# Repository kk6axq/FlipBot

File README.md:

# FlipBot
FlipBot is a small two wheeled robot development platform. It was developed over the Spring 2021 semester as an honors contract project for EGR102, at Arizona State University on the Polytechnic Campus, under the guidance of Dr. Daniel Frank. The goal for this project was to develop a small robot platform and to gain a better understanding of the design considerations in designing a complete system. Where possible, this project attempted to integrate components directly into the design, rather than using breakout boards or modules.

 ## Components
 There are several major components of FlipBot:
 * **Controller.** The robot is controlled by a wireless remote connected to a Wii Nunchuk. This provides a joystick, two buttons, and pitch/roll data that is processed by a microcontroller and sent wirelessly to the main controller onboard the robot. The controller also has onboard battery management hardware to enable operation from a single 18650 battery.

 * **Wireless link.** The controller and robot use NRF24 radio modules to communicate. These operate in the 2.4GHz ISM band and provide low latency, medium range. While they have the ability to confirm packet reception, in this application the controller sends packets regardless of whether the received is in range or able to respond.
 * **Onboard Power Management.** This project was developed in conjunction with a second honors contract to develop a power management board for use with LiPo batteries. This PCB provides intelligent power monitoring capabilities on the robot. More information about this part is available in the project repository: [https://github.com/kk6axq/PowerMonitor/](https://github.com/kk6axq/PowerMonitor/).

 * **Orientation Sensing.** An onboard MPU6050 accelerometer/gyro provides onboard orientation detection, enabling the controls to be reversed if the robot flips upside down.
 * **Main Board.** The main PCB interfaces to the radio, orientation sensor, and the power management board, in addition to providing motor control and processing input from the motor's encoders (not yet implemented).

## Project Status
Due to incomplete design verification and limited time, the project was not able to achieve full functionality before the end of the semester. The level converter responsible for interfacing between the motor controllers and the microcontroller was not properly matched to the application and would not properly convert, leading the motor controllers to operate sporadically.

This issue, in addition to a few minor routing decisions, is due to be fixed during a revision of the main board scheduled for Summer 2021, with the hope that the project will be functional by Fall 2021.

**Update Fall 2021:** Over the summer, the hardware design issues were mitigated within the existing PCB and a new PCB was milled for the controller. There still remain some phantom issues with controller connectivity and some larger issues with the initial current draw of the motor controllers. At this point, the project is at a holding point, and may or may not see further development.

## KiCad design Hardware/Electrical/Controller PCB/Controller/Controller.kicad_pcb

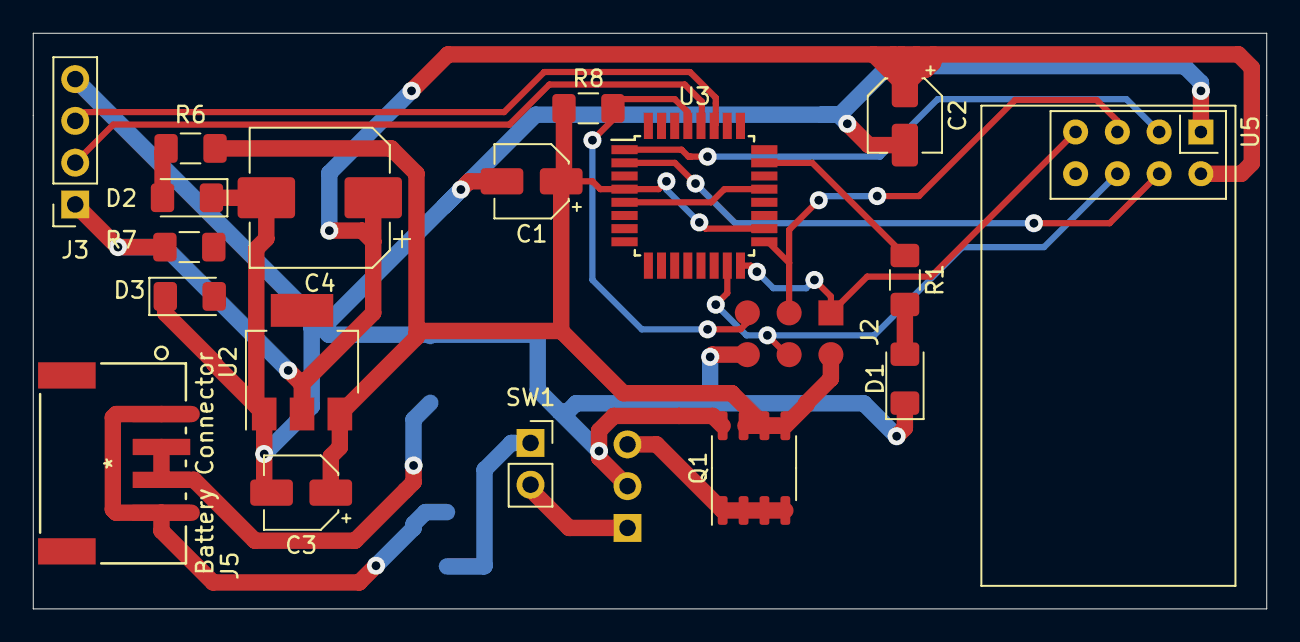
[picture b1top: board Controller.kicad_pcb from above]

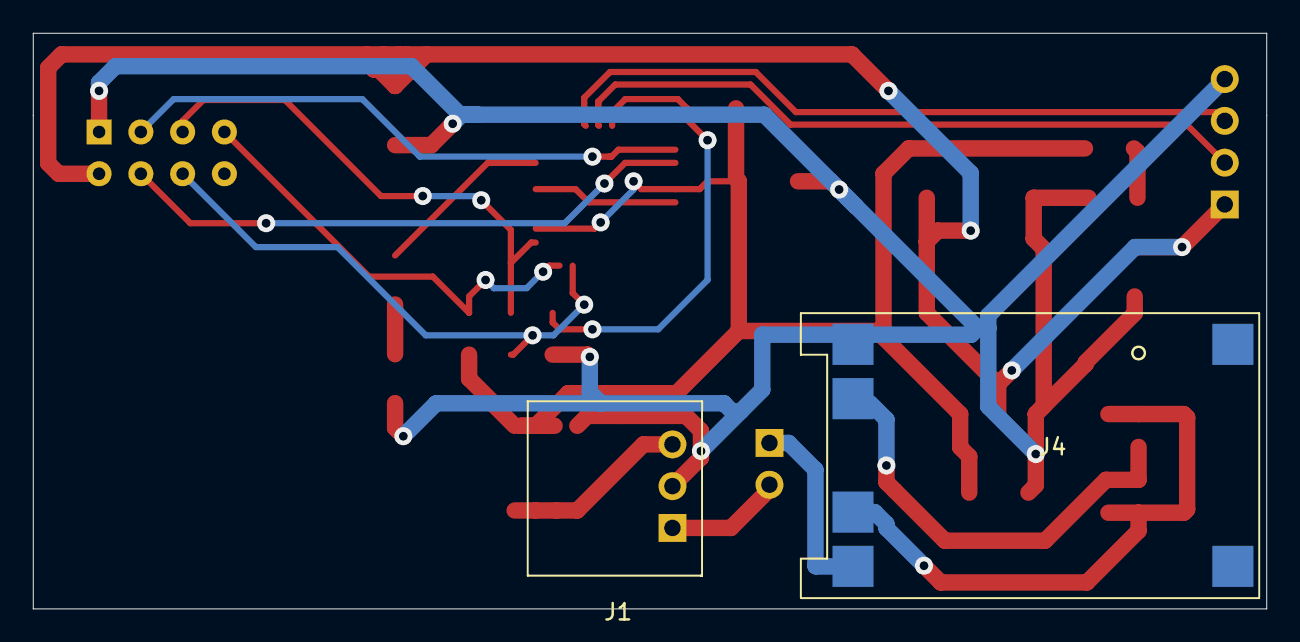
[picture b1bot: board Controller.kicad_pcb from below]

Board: 2 copper layers, 75.0 x 35.0 mm, 21 parts (2 on the bottom side), 21 nets.

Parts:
C1, C2, C3: 10uF; CP_Elec_4x3.9
C4: 100uF; CP_Elec_8x10
D1, D2: Red; LED_1206_3216Metric_Pad1.42x1.75mm_HandSolder
D3: Green; LED_1206_3216Metric_Pad1.42x1.75mm_HandSolder
J1: Boost Board; Boost_Converter
J2: AVR-ISP-6; ICSP
J3: Nunchuk Connector; PinSocket_1x04_P2.54mm_Vertical
J4: Charge Controller; Battery_Manager
J5: Battery Connector; S4B-PH-SM4-TBLFSN
Q1: Si4435FDY; Si4435
R1, R6: 330; R_1206_3216Metric_Pad1.42x1.75mm_HandSolder
R7: 220; R_1206_3216Metric_Pad1.42x1.75mm_HandSolder
R8: 10k; R_1206_3216Metric_Pad1.42x1.75mm_HandSolder
SW1: SW_SPST; PinSocket_1x02_P2.54mm_Vertical
U2: LM1117-3.3; SOT-223
U3: ATtiny88-AU; TQFP-32_7x7mm_P0.8mm
U5: NRF24L01_Breakout; nRF24L01_Breakout

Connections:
+3V3: C2.1, C4.1, J3.1, R7.1, U2.2, U5.2
+5V: C1.1, C3.1, J2.2, Q1.1, Q1.2, Q1.3, R6.1, R8.1, U2.3, U3.4, U3.18
CE: U3.1, U5.3
CSN: U3.2, U5.4
GND: C1.2, C2.2, C3.2, C4.2, D1.1, D2.1, D3.1, J1.2, J2.6, J3.4, J4.4, Q1.4, U2.1, U5.1
LED_STATUS: R1.1, U3.23
MISO: J2.1, U3.16, U5.7
MOSI: J2.4, U3.15, U5.6
unnamed: D1.2, R1.2
unnamed: D2.2, R6.2
unnamed: D3.2, R7.2
unnamed: J1.1, SW1.2
unnamed: J1.3, Q1.5, Q1.6, Q1.7, Q1.8
unnamed: J4.1, SW1.1
unnamed: J4.2, J5.1, J5.4
unnamed: J4.3, J5.2, J5.3
unnamed: U3.5, U3.21
RST: J2.5, R8.2, U3.29
SCK: J2.3, U3.17, U5.5
SCL: J3.2, U3.28
SDA: J3.3, U3.27

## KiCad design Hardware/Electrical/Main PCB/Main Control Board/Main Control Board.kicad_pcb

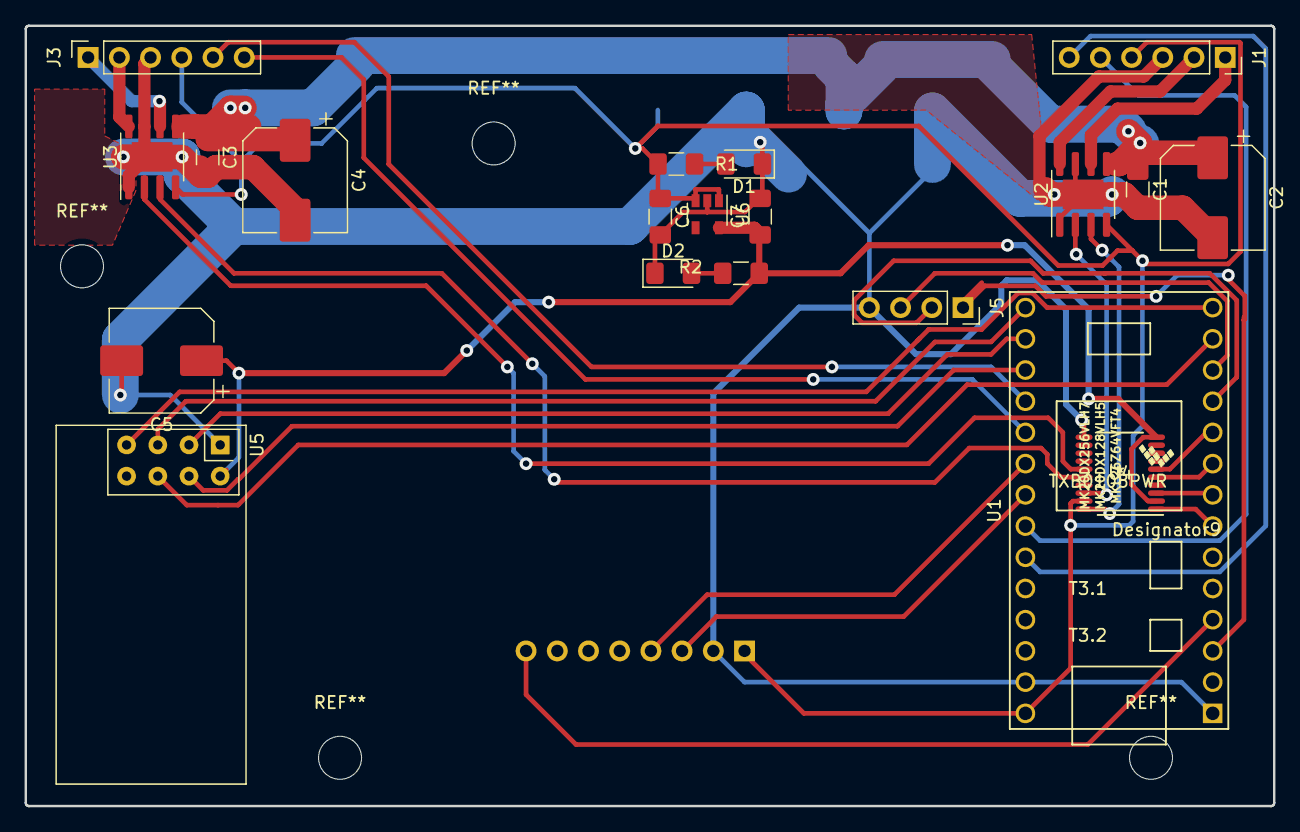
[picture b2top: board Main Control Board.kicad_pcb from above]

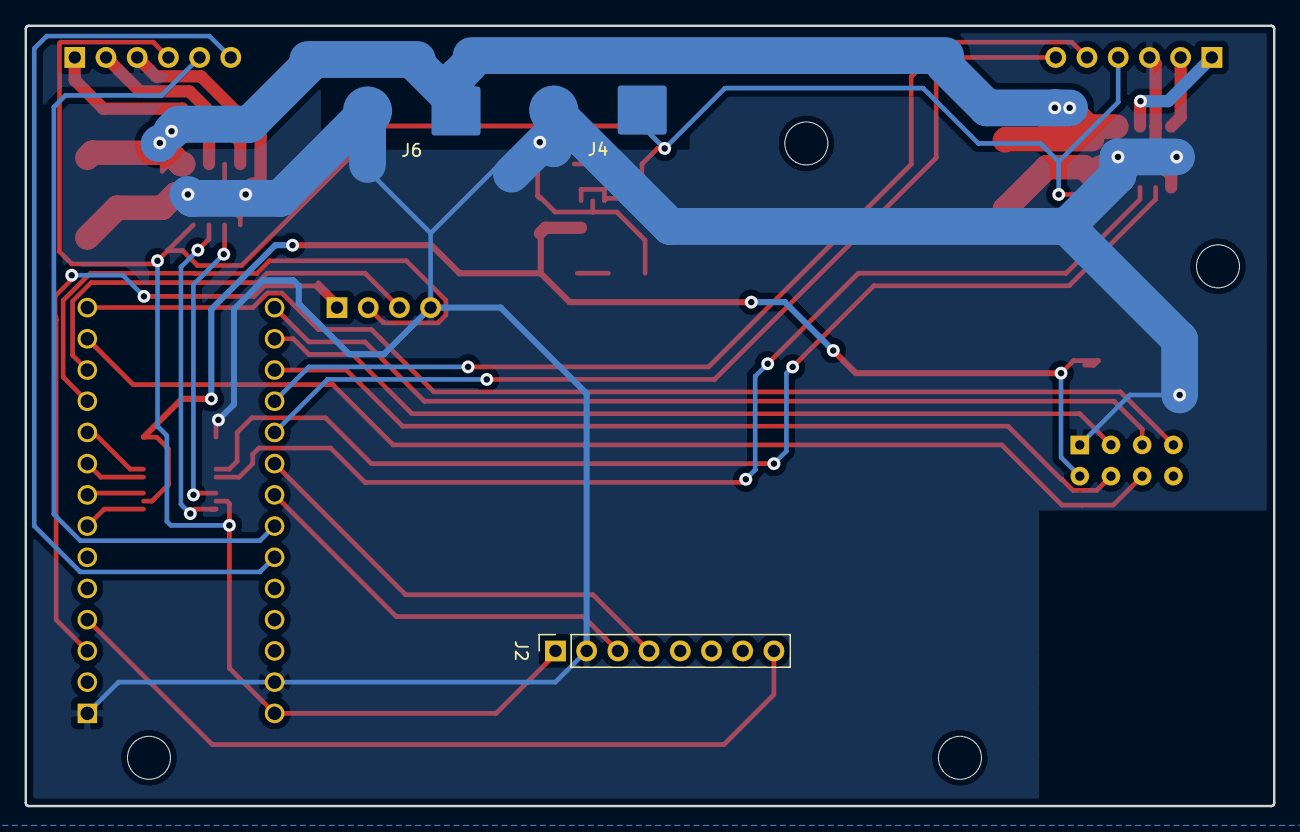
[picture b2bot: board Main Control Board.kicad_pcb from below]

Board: 2 copper layers, 101.6 x 63.5 mm, 23 parts (3 on the bottom side), 33 nets.

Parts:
C1, C3: 0.22uF 50V X5R; C_1206_3216Metric_Pad1.42x1.75mm_HandSolder
C2, C4: 100uF 50V Electrolytic; CP_Elec_8x10
C5: 100uF; CP_Elec_8x10
C6, C7: 1uF; C_1206_3216Metric_Pad1.42x1.75mm_HandSolder
D1: RED; D_1206_3216Metric_Pad1.42x1.75mm_HandSolder
D2: GREEN; D_1206_3216Metric_Pad1.42x1.75mm_HandSolder
J1: Motor 1 Connector; PinSocket_1x06_P2.54mm_Vertical
J2: MPU6050 GY-521 Breakout; PinSocket_1x08_P2.54mm_Vertical
J3: Motor 2 Connector; PinSocket_1x06_P2.54mm_Vertical
J4: 5V Power; SolderWire-2.5sqmm_1x02_P7.2mm_D2.4mm_OD3.6mm_SMD
J5: Payload Connector; PinSocket_1x04_P2.54mm_Vertical
J6: 12V Power; SolderWire-2.5sqmm_1x02_P7.2mm_D2.4mm_OD3.6mm_SMD
R1: 330; R_1206_3216Metric_Pad1.42x1.75mm_HandSolder
R2: 220; R_1206_3216Metric_Pad1.42x1.75mm_HandSolder
U1: Teensy3.2; Teensy30_31_32_LC_No_Center_Pins
U2, U3: A4950E; SOIC-8-1EP_3.9x4.9mm_P1.27mm_EP2.41x3.3mm
U4: TXB0108PWR
U5: NRF24L01_Breakout; nRF24L01_Breakout
U6: MIC5504-3.3YM5; SOT-23-5

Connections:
+3V3: C5.1, C7.1, R2.1, U4.2, U4.10, U5.2, U6.5
+5V: C6.1, J1.4, J2.1, J3.4, J4.1, R1.1, U1.33, U2.4, U3.4, U4.19, U6.1, U6.3
+12V: C1.1, C2.1, C3.1, C4.1, J6.1, U2.5, U3.5
CE: U1.21, U5.3
CSN: U1.22, U5.4
GND: C1.2, C2.2, C3.2, C4.2, C5.2, C6.2, C7.2, D1.1, D2.1, J1.3, J2.2, J3.3, J4.2, J5.4, J6.2, U1.1, U1.32, U2.1, U2.7, U2.9, U3.1, U3.7, U3.9, U4.11, U5.1, U6.2
M1+: J1.1, U2.6
M1-: J1.2, U2.8
M1_ENCA: J1.5, U1.27
M1_ENCB: J1.6, U1.28
M1_IN1: U2.3, U4.20
M1_IN2: U2.2, U4.18
M2+: J3.1, U3.6
M2-: J3.2, U3.8
M2_ENCA: J3.5, U1.23
M2_ENCB: J3.6, U1.24
M2_IN1: U3.3, U4.16
M2_IN2: U3.2, U4.15
MCU_M1_IN1: U1.7, U4.1
MCU_M1_IN2: U1.8, U4.3
MCU_M2_IN1: U1.9, U4.5
MCU_M2_IN2: U1.10, U4.6
MISO: U1.14, U5.7
MOSI: U1.13, U5.6
MPU_INT: J2.8, U1.4
MPU_SCL: J2.3, U1.26
MPU_SDA: J2.4, U1.25
unnamed: D1.2, R1.2
unnamed: D2.2, R2.2
PAYLOAD_SCL: J5.2, U1.11
PAYLOAD_SDA: J5.3, U1.12
PAYLOAD_SHUTDOWN: J5.1, U1.3
SCK: U1.20, U5.5

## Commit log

2021-04-08 Add Hardware Files
2021-04-09 Add more hardware and software files
2021-04-09 Add block diagram image
2021-04-13 Add media and more documentation
2021-04-13 Add more documentation and photos
2021-04-13 Fix typo
2021-04-20 Add BOM
2021-04-20 Add project report
2021-04-20 Replace project report with PDF version
2021-09-24 Add photos
2021-09-24 Add photos and project update

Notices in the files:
parts and their libraries:
Copyright 2016 Accelerated Designs. All rights reserved.
